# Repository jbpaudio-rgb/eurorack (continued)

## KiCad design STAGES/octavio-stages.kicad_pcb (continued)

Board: 2 copper layers, 242 parts (161 on the bottom side), 190 nets, no tracks yet.

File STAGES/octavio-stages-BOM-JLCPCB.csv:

Comment,Designator,Footprint,LCSC Part #,Notes
Raspberry Pi Pico,A1,RaspberryPi_Pico_Headers,,"Raspberry Pi Pico (RP2040) sur 2 barrettes femelles 1x20 2,54 mm, 8,5 mm (soudées à la main) - THT (wave soldering) - laisser JLC choisir (Basic de preference)"
10u 25V X5R/X7R 1206,"C1,C2,C3",C_1206_3216Metric,,X5R/X7R 1206 - SMT bottom - laisser JLC choisir (Basic de preference)
100p,"C16,C17",C_0603_1608Metric,,SMT bottom - laisser JLC choisir (Basic de preference)
10u 25V X5R/X7R 1206,C4,C_1206_3216Metric,,"X5R/X7R 1206 (3,3 V des potentiomètres) - SMT bottom - laisser JLC choisir (Basic de preference)"
100n,"C5,C6,C9,C10,C11,C12,C13,C14,C15,C18,C19,C20,C21,C22,C23,C24,C25",C_0603_1608Metric,,SMT bottom - laisser JLC choisir (Basic de preference)
10n,"C7,C8",C_0603_1608Metric,,SMT bottom - laisser JLC choisir (Basic de preference)
SS14,"D1,D2",D_SMA,,SS14 (40 V 1 A Schottky) - SMT bottom - laisser JLC choisir (Basic de preference)
LED,"D10,D11,D12,D13,D14,D15,D16,D17",LED_D3.0mm,,LED 3 mm ambre (SLIDE) - THT (wave soldering) - laisser JLC choisir (Basic de preference)
LED,"D20,D21,D22,D23,D24,D25,D26,D27",LED_D3.0mm,,LED 3 mm rouge (étape) - THT (wave soldering) - laisser JLC choisir (Basic de preference)
SS14,D3,D_SMA,,SS14 (Schottky : USB et rack peuvent être branchés ensemble) - SMT bottom - laisser JLC choisir (Basic de preference)
LED,"D30,D31,D32",LED_D3.0mm,,LED 3 mm ambre (mode) - THT (wave soldering) - laisser JLC choisir (Basic de preference)
BAT54S,"D4,D5",SOT-23,,BAT54S (protection ADC) - SMT bottom - laisser JLC choisir (Basic de preference)
Eurorack 2x5,J1,IDC-Header_2x05_P2.54mm_Vertical,,Shrouded header 2x5 2.54 mm - THT (wave soldering) - laisser JLC choisir (Basic de preference)
GATE,J10,Jack_3.5mm_Thonkiconn_PJ398SM,C9900080080,QingPu WQP-PJ301M-12 (Thonkiconn) - THT (wave soldering)
SEL 1,J11,Jack_3.5mm_Thonkiconn_PJ398SM,C9900080080,QingPu WQP-PJ301M-12 (Thonkiconn) - THT (wave soldering)
SEL 2,J12,Jack_3.5mm_Thonkiconn_PJ398SM,C9900080080,QingPu WQP-PJ301M-12 (Thonkiconn) - THT (wave soldering)
SEL 3,J13,Jack_3.5mm_Thonkiconn_PJ398SM,C9900080080,QingPu WQP-PJ301M-12 (Thonkiconn) - THT (wave soldering)
SEL 4,J14,Jack_3.5mm_Thonkiconn_PJ398SM,C9900080080,QingPu WQP-PJ301M-12 (Thonkiconn) - THT (wave soldering)
SEL 5,J15,Jack_3.5mm_Thonkiconn_PJ398SM,C9900080080,QingPu WQP-PJ301M-12 (Thonkiconn) - THT (wave soldering)
SEL 6,J16,Jack_3.5mm_Thonkiconn_PJ398SM,C9900080080,QingPu WQP-PJ301M-12 (Thonkiconn) - THT (wave soldering)
SEL 7,J17,Jack_3.5mm_Thonkiconn_PJ398SM,C9900080080,QingPu WQP-PJ301M-12 (Thonkiconn) - THT (wave soldering)
SEL 8,J18,Jack_3.5mm_Thonkiconn_PJ398SM,C9900080080,QingPu WQP-PJ301M-12 (Thonkiconn) - THT (wave soldering)
GATE 1,J19,Jack_3.5mm_Thonkiconn_PJ398SM,C9900080080,QingPu WQP-PJ301M-12 (Thonkiconn) - THT (wave soldering)
CLOCK,J2,Jack_3.5mm_Thonkiconn_PJ398SM,C9900080080,QingPu WQP-PJ301M-12 (Thonkiconn) - THT (wave soldering)
GATE 2,J20,Jack_3.5mm_Thonkiconn_PJ398SM,C9900080080,QingPu WQP-PJ301M-12 (Thonkiconn) - THT (wave soldering)
GATE 3,J21,Jack_3.5mm_Thonkiconn_PJ398SM,C9900080080,QingPu WQP-PJ301M-12 (Thonkiconn) - THT (wave soldering)
GATE 4,J22,Jack_3.5mm_Thonkiconn_PJ398SM,C9900080080,QingPu WQP-PJ301M-12 (Thonkiconn) - THT (wave soldering)
GATE 5,J23,Jack_3.5mm_Thonkiconn_PJ398SM,C9900080080,QingPu WQP-PJ301M-12 (Thonkiconn) - THT (wave soldering)
GATE 6,J24,Jack_3.5mm_Thonkiconn_PJ398SM,C9900080080,QingPu WQP-PJ301M-12 (Thonkiconn) - THT (wave soldering)
GATE 7,J25,Jack_3.5mm_Thonkiconn_PJ398SM,C9900080080,QingPu WQP-PJ301M-12 (Thonkiconn) - THT (wave soldering)
GATE 8,J26,Jack_3.5mm_Thonkiconn_PJ398SM,C9900080080,QingPu WQP-PJ301M-12 (Thonkiconn) - THT (wave soldering)
START,J3,Jack_3.5mm_Thonkiconn_PJ398SM,C9900080080,QingPu WQP-PJ301M-12 (Thonkiconn) - THT (wave soldering)
STROBE,J4,Jack_3.5mm_Thonkiconn_PJ398SM,C9900080080,QingPu WQP-PJ301M-12 (Thonkiconn) - THT (wave soldering)
TIME CV,J5,Jack_3.5mm_Thonkiconn_PJ398SM,C9900080080,QingPu WQP-PJ301M-12 (Thonkiconn) - THT (wave soldering)
ANALOG,J6,Jack_3.5mm_Thonkiconn_PJ398SM,C9900080080,QingPu WQP-PJ301M-12 (Thonkiconn) - THT (wave soldering)
END,J7,Jack_3.5mm_Thonkiconn_PJ398SM,C9900080080,QingPu WQP-PJ301M-12 (Thonkiconn) - THT (wave soldering)
CV A,J8,Jack_3.5mm_Thonkiconn_PJ398SM,C9900080080,QingPu WQP-PJ301M-12 (Thonkiconn) - THT (wave soldering)
CV B,J9,Jack_3.5mm_Thonkiconn_PJ398SM,C9900080080,QingPu WQP-PJ301M-12 (Thonkiconn) - THT (wave soldering)
BC847C,"Q1,Q2,Q3,Q4,Q5,Q6,Q7,Q8,Q9,Q10,Q11",SOT-23,,BC847C - SMT bottom - laisser JLC choisir (Basic de preference)
100k 1% 0805,"R1,R5,R9,R10,R12,R13,R15,R16,R18,R19,R21,R22,R24,R25,R27,R28,R30,R31,R33,R34,R36,R37,R39,R40",R_0603_1608Metric,,SMT bottom - laisser JLC choisir (Basic de preference)
38k3 1% 0805,"R100,R103",R_0603_1608Metric,,SMT bottom - laisser JLC choisir (Basic de preference)
10k 1% 0805,"R11,R14,R17,R20,R23,R26,R29,R32,R35,R38,R41,R42,R43,R44,R45,R46,R47,R48,R49,R69,R72,R75,R78,R81,R84,R87,R90,R93,R96,R99,R102",R_0603_1608Metric,,SMT bottom - laisser JLC choisir (Basic de preference)
15k 1% 0805,"R2,R6",R_0603_1608Metric,,SMT bottom - laisser JLC choisir (Basic de preference)
110k 1% 0805,"R3,R7",R_0603_1608Metric,,SMT bottom - laisser JLC choisir (Basic de preference)
1k 1% 0805,"R4,R8,R50,R51,R52,R53,R54,R55,R56,R57,R58,R59,R60,R61,R62,R63,R64,R65,R66,R67,R68,R71,R74,R77,R80,R83,R86,R89,R92,R95,R98,R101,R104",R_0603_1608Metric,,SMT bottom - laisser JLC choisir (Basic de preference)
20k 1% 0805,"R70,R73,R76,R79,R82,R85,R88,R91,R94,R97",R_0603_1608Metric,,SMT bottom - laisser JLC choisir (Basic de preference)
10k B,"RV1,RV2,RV3,RV4,RV5,RV6,RV7,RV8,RV9,RV10,RV11,RV12,RV13,RV14,RV15,RV16,RV17,RV18,RV19,RV20,RV21,RV22,RV23,RV24,RV25,RV26,RV27",Pot_Alpha_9mm_Vertical,,"POT-R09V-10K (9 mm vertical, B10k) - THT (wave soldering) - laisser JLC choisir (Basic de preference)"
SW,"SW1,SW2,SW3,SW4,SW5,SW6,SW7,SW8,SW9,SW10",Tactile_6mm_THT_Panel,,"Bouton 6x6 mm THT à tige longue (ex. TS-1187A-B-A-B / C&K PTS645, capuchon rond) - THT (wave soldering) - laisser JLC choisir (Basic de preference)"
AMS1117-5.0,U1,SOT-223-3_TabPin2,,AMS1117-5.0 (C6187) - SMT bottom - laisser JLC choisir (Basic de preference)
MCP4822-E/SN,U10,SOIC-8_3.9x4.9mm_P1.27mm,,MCP4822-E/SN - SMT bottom - laisser JLC choisir (Basic de preference)
TL074CDR,"U11,U12,U13,U14",SOIC-14_3.9x8.7mm_P1.27mm,C12594,TL074CDR - SMT bottom
74HC4067 CD74HC4067M96,"U2,U3",SOIC-24W_7.5x15.4mm_P1.27mm,,CD74HC4067M96 - SMT bottom - laisser JLC choisir (Basic de preference)
74HC165D,"U4,U5",SOIC-16_3.9x9.9mm_P1.27mm,,74HC165D - SMT bottom - laisser JLC choisir (Basic de preference)
74HC595D,"U6,U7,U8,U9",SOIC-16_3.9x9.9mm_P1.27mm,,74HC595D - SMT bottom - laisser JLC choisir (Basic de preference)

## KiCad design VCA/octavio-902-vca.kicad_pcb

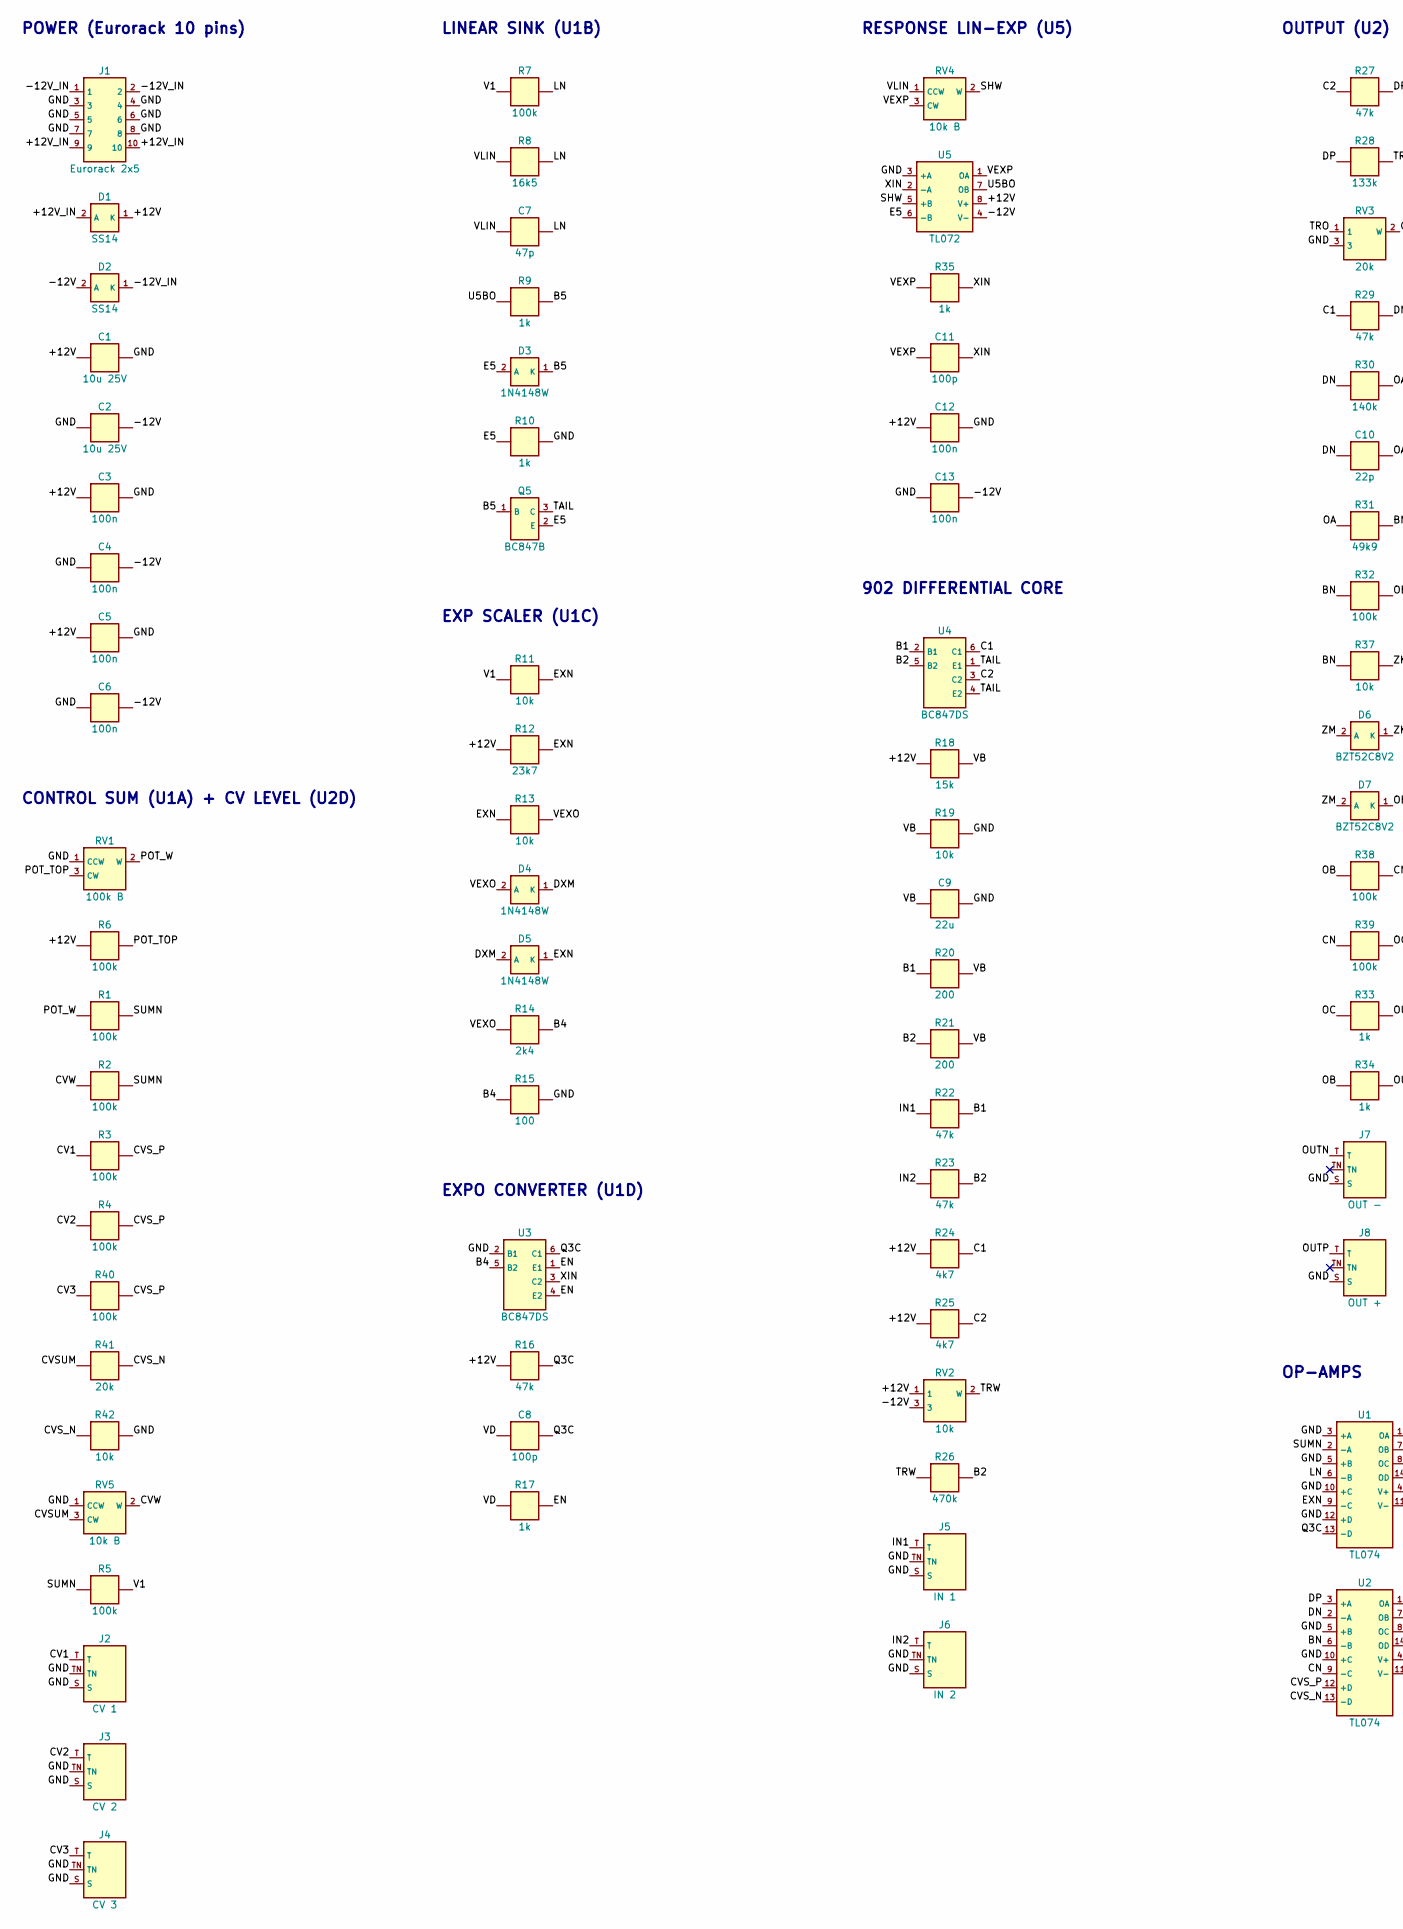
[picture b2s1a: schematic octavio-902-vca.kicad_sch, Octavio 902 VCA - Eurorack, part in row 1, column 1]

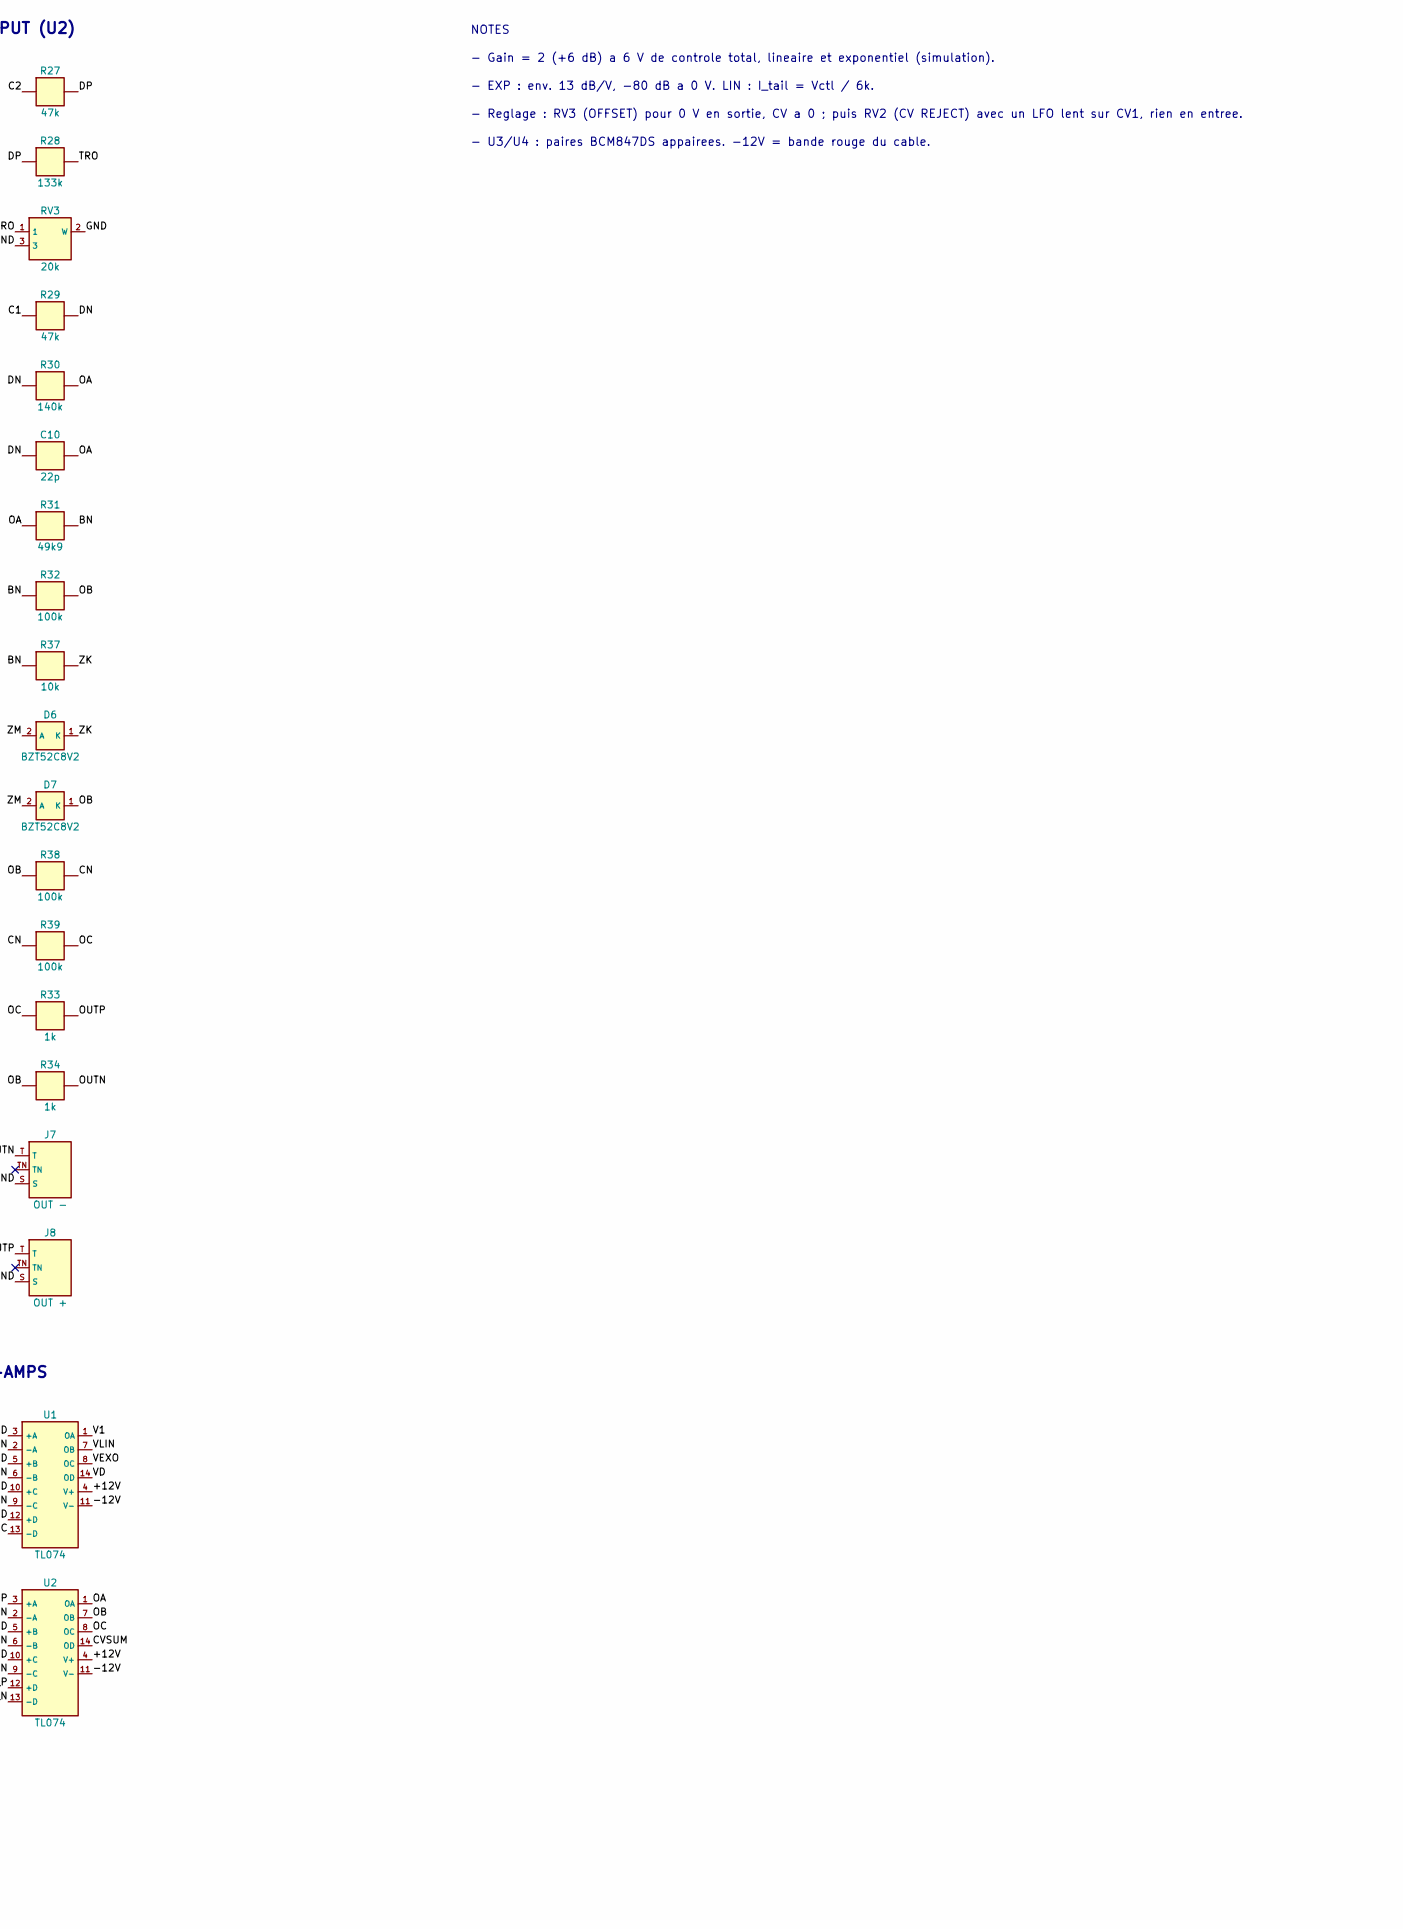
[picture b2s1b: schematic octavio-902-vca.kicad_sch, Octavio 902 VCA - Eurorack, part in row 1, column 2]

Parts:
C1, C2: 10u 25V; C_1206_3216Metric; MPN X5R/X7R 1206
C3, C4, C5, C6, C12, C13: 100n; C_0805_2012Metric
C7: 47p; C_0805_2012Metric
C8, C11: 100p; C_0805_2012Metric
C9: 22u; C_1206_3216Metric; MPN X5R 1206 16 V
C10: 22p; C_0805_2012Metric
D1, D2: SS14; D_SMA; MPN SS14 (40 V 1 A Schottky)
D3, D4, D5: 1N4148W; D_SOD-123; MPN 1N4148W
D6, D7: BZT52C8V2; D_SOD-123; MPN BZT52C8V2 (zener 8,2 V)
J1: Eurorack 2x5; IDC-Header_2x05_P2.54mm_Vertical; MPN Shrouded header 2x5 2.54 mm
J2: CV 1; Jack_3.5mm_Thonkiconn_PJ398SM; MPN QingPu WQP-PJ301M-12 (Thonkiconn)
J3: CV 2; Jack_3.5mm_Thonkiconn_PJ398SM; MPN QingPu WQP-PJ301M-12 (Thonkiconn)
J4: CV 3; Jack_3.5mm_Thonkiconn_PJ398SM; MPN QingPu WQP-PJ301M-12 (Thonkiconn)
J5: IN 1; Jack_3.5mm_Thonkiconn_PJ398SM; MPN QingPu WQP-PJ301M-12 (Thonkiconn)
J6: IN 2; Jack_3.5mm_Thonkiconn_PJ398SM; MPN QingPu WQP-PJ301M-12 (Thonkiconn)
J7: OUT -; Jack_3.5mm_Thonkiconn_PJ398SM; MPN QingPu WQP-PJ301M-12 (Thonkiconn)
J8: OUT +; Jack_3.5mm_Thonkiconn_PJ398SM; MPN QingPu WQP-PJ301M-12 (Thonkiconn)
Q5: BC847B; SOT-23; MPN BC847B
R1, R2, R3, R4, R5, R6, R7, R32, R38, R39, R40: 100k; R_0805_2012Metric
R8: 16k5; R_0805_2012Metric
R9, R10, R17, R33, R34, R35: 1k; R_0805_2012Metric
R11, R13, R19, R37, R42: 10k; R_0805_2012Metric
R12: 23k7; R_0805_2012Metric
R14: 2k4; R_0805_2012Metric
R15: 100; R_0805_2012Metric
R16, R22, R23, R27, R29: 47k; R_0805_2012Metric
R18: 15k; R_0805_2012Metric
R20, R21: 200; R_0805_2012Metric
R24, R25: 4k7; R_0805_2012Metric
R26: 470k; R_0805_2012Metric
R28: 133k; R_0805_2012Metric
R30: 140k; R_0805_2012Metric
R31: 49k9; R_0805_2012Metric
R41: 20k; R_0805_2012Metric
RV1: 100k B; Pot_Alpha_9mm_Vertical; MPN POT-R09V-100K (9 mm vertical, B100k)
RV2: 10k; Potentiometer_Bourns_3362P_Vertical; MPN Bourns 3362P-1-103LF
RV3: 20k; Potentiometer_Bourns_3362P_Vertical; MPN Bourns 3362P-1-203LF
RV4, RV5: 10k B; Pot_Alpha_9mm_Vertical; MPN POT-R09V-10K (9 mm vertical, B10k)
U1, U2: TL074; SOIC-14_3.9x8.7mm_P1.27mm; MPN TL074CDR
U3, U4: BC847DS; SOT-457; MPN BC847DS,115 (Nexperia, paire double)
U5: TL072; SOIC-8_3.9x4.9mm_P1.27mm; MPN TL072CDR

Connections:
+12V: C1.1, C3.1, C5.1, C12.1, D1.1 (K), R6.1, R12.1, R16.1, R18.1, R24.1, R25.1, RV2.1, U1.4 (V+), U2.4 (V+), U5.8 (V+)
+12V_IN: D1.2 (A), J1.9, J1.10
-12V: C2.2, C4.2, C6.2, C13.2, D2.2 (A), RV2.3, U1.11 (V-), U2.11 (V-), U5.4 (V-)
-12V_IN: D2.1 (K), J1.1, J1.2
B1: R20.1, R22.2, U4.2 (B1)
B2: R21.1, R23.2, R26.2, U4.5 (B2)
B4: R14.2, R15.1, U3.5 (B2)
B5: D3.1 (K), Q5.1 (B), R9.2
BN: R31.2, R32.1, R37.1, U2.6 (-B)
C1: R24.2, R29.1, U4.6 (C1)
C2: R25.2, R27.1, U4.3 (C2)
CN: R38.2, R39.1, U2.9 (-C)
CV1: J2.T, R3.1
CV2: J3.T, R4.1
CV3: J4.T, R40.1
CVSUM: R41.1, RV5.3 (CW), U2.14 (OD)
CVS_N: R41.2, R42.1, U2.13 (-D)
CVS_P: R3.2, R4.2, R40.2, U2.12 (+D)
CVW: R2.1, RV5.2 (W)
DN: C10.1, R29.2, R30.1, U2.2 (-A)
DP: R27.2, R28.1, U2.3 (+A)
DXM: D4.1 (K), D5.2 (A)
E5: D3.2 (A), Q5.2 (E), R10.1, U5.6 (-B)
EN: R17.2, U3.1 (E1), U3.4 (E2)
EXN: D5.1 (K), R11.2, R12.2, R13.1, U1.9 (-C)
GND: C1.2, C2.1, C3.2, C4.1, C5.2, C6.1, C9.2, C12.2, C13.1, J1.3, J1.4, J1.5, J1.6, J1.7, J1.8, J2.S, J2.TN, J3.S, J3.TN, J4.S, J4.TN, J5.S, J5.TN, J6.S, J6.TN, J7.S, J8.S, R10.2, R15.2, R19.2, R42.2, RV1.1 (CCW), RV3.2 (W), RV3.3, RV5.1 (CCW), U1.3 (+A), U1.5 (+B), U1.10 (+C), U1.12 (+D), U2.5 (+B), U2.10 (+C), U3.2 (B1), U5.3 (+A)
IN1: J5.T, R22.1
IN2: J6.T, R23.1
LN: C7.2, R7.2, R8.2, U1.6 (-B)
OA: C10.2, R30.2, R31.1, U2.1 (OA)
OB: D7.1 (K), R32.2, R34.1, R38.1, U2.7 (OB)
OC: R33.1, R39.2, U2.8 (OC)
OUTN: J7.T, R34.2
OUTP: J8.T, R33.2
POT_TOP: R6.2, RV1.3 (CW)
POT_W: R1.1, RV1.2 (W)
Q3C: C8.2, R16.2, U1.13 (-D), U3.6 (C1)
SHW: RV4.2 (W), U5.5 (+B)
SUMN: R1.2, R2.2, R5.1, U1.2 (-A)
TAIL: Q5.3 (C), U4.1 (E1), U4.4 (E2)
TRO: R28.2, RV3.1
TRW: R26.1, RV2.2 (W)
U5BO: R9.1, U5.7 (OB)
V1: R5.2, R7.1, R11.1, U1.1 (OA)
VB: C9.1, R18.2, R19.1, R20.2, R21.2
VD: C8.1, R17.1, U1.14 (OD)
VEXO: D4.2 (A), R13.2, R14.1, U1.8 (OC)
VEXP: C11.1, R35.1, RV4.3 (CW), U5.1 (OA)
VLIN: C7.1, R8.1, RV4.1 (CCW), U1.7 (OB)
XIN: C11.2, R35.2, U3.3 (C2), U5.2 (-A)
ZK: D6.1 (K), R37.2
ZM: D6.2 (A), D7.2 (A)

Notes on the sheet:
POWER (Eurorack 10 pins)
CONTROL SUM (U1A) + CV LEVEL (U2D)
LINEAR SINK (U1B)
EXP SCALER (U1C)
EXPO CONVERTER (U1D)
RESPONSE LIN-EXP (U5)
902 DIFFERENTIAL CORE
OUTPUT (U2)
OP-AMPS
NOTES
- Gain = 2 (+6 dB) a 6 V de controle total, lineaire et exponentiel (simulation).
- EXP : env. 13 dB/V, -80 dB a 0 V. LIN : I_tail = Vctl / 6k.
- Reglage : RV3 (OFFSET) pour 0 V en sortie, CV a 0 ; puis RV2 (CV REJECT) avec un LFO lent sur CV1, rien en entree.
- U3/U4 : paires BCM847DS appairees. -12V = bande rouge du cable.

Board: 2 copper layers, 80 parts (70 on the bottom side), 52 nets, no tracks yet.

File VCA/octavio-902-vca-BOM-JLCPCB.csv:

Comment,Designator,Footprint,LCSC Part #,Notes
10u 25V X5R/X7R 1206,"C1,C2",C_1206_3216Metric,,X5R/X7R 1206 - SMT bottom - laisser JLC choisir (Basic de preference)
22p,C10,C_0805_2012Metric,,SMT bottom - laisser JLC choisir (Basic de preference)
100n,"C3,C4,C5,C6,C12,C13",C_0805_2012Metric,,SMT bottom - laisser JLC choisir (Basic de preference)
47p,C7,C_0805_2012Metric,,SMT bottom - laisser JLC choisir (Basic de preference)
100p,"C8,C11",C_0805_2012Metric,,SMT bottom - laisser JLC choisir (Basic de preference)
22u X5R 1206 16 V,C9,C_1206_3216Metric,,X5R 1206 16 V - SMT bottom - laisser JLC choisir (Basic de preference)
SS14,"D1,D2",D_SMA,,SS14 (40 V 1 A Schottky) - SMT bottom - laisser JLC choisir (Basic de preference)
1N4148W,"D3,D4,D5",D_SOD-123,,1N4148W - SMT bottom - laisser JLC choisir (Basic de preference)
BZT52C8V2,"D6,D7",D_SOD-123,,"BZT52C8V2 (zener 8,2 V) - SMT bottom - laisser JLC choisir (Basic de preference)"
Eurorack 2x5,J1,IDC-Header_2x05_P2.54mm_Vertical,,Shrouded header 2x5 2.54 mm - THT (wave soldering) - laisser JLC choisir (Basic de preference)
CV 1,J2,Jack_3.5mm_Thonkiconn_PJ398SM,C9900080080,QingPu WQP-PJ301M-12 (Thonkiconn) - THT (wave soldering)
CV 2,J3,Jack_3.5mm_Thonkiconn_PJ398SM,C9900080080,QingPu WQP-PJ301M-12 (Thonkiconn) - THT (wave soldering)
CV 3,J4,Jack_3.5mm_Thonkiconn_PJ398SM,C9900080080,QingPu WQP-PJ301M-12 (Thonkiconn) - THT (wave soldering)
IN 1,J5,Jack_3.5mm_Thonkiconn_PJ398SM,C9900080080,QingPu WQP-PJ301M-12 (Thonkiconn) - THT (wave soldering)
IN 2,J6,Jack_3.5mm_Thonkiconn_PJ398SM,C9900080080,QingPu WQP-PJ301M-12 (Thonkiconn) - THT (wave soldering)
OUT -,J7,Jack_3.5mm_Thonkiconn_PJ398SM,C9900080080,QingPu WQP-PJ301M-12 (Thonkiconn) - THT (wave soldering)
OUT +,J8,Jack_3.5mm_Thonkiconn_PJ398SM,C9900080080,QingPu WQP-PJ301M-12 (Thonkiconn) - THT (wave soldering)
BC847B,Q5,SOT-23,,BC847B - SMT bottom - laisser JLC choisir (Basic de preference)
23k7 1% 0805,R12,R_0805_2012Metric,,SMT bottom - laisser JLC choisir (Basic de preference)
2k4 1% 0805,R14,R_0805_2012Metric,,SMT bottom - laisser JLC choisir (Basic de preference)
100 1% 0805,R15,R_0805_2012Metric,,SMT bottom - laisser JLC choisir (Basic de preference)
47k 1% 0805,"R16,R22,R23,R27,R29",R_0805_2012Metric,,SMT bottom - laisser JLC choisir (Basic de preference)
15k 1% 0805,R18,R_0805_2012Metric,,SMT bottom - laisser JLC choisir (Basic de preference)
200 1% 0805,"R20,R21",R_0805_2012Metric,,SMT bottom - laisser JLC choisir (Basic de preference)
4k7 1% 0805,"R24,R25",R_0805_2012Metric,,SMT bottom - laisser JLC choisir (Basic de preference)
470k 1% 0805,R26,R_0805_2012Metric,,SMT bottom - laisser JLC choisir (Basic de preference)
133k 1% 0805,R28,R_0805_2012Metric,,SMT bottom - laisser JLC choisir (Basic de preference)
140k 1% 0805,R30,R_0805_2012Metric,,SMT bottom - laisser JLC choisir (Basic de preference)
49k9 1% 0805,R31,R_0805_2012Metric,,SMT bottom - laisser JLC choisir (Basic de preference)
20k 1% 0805,R41,R_0805_2012Metric,,SMT bottom - laisser JLC choisir (Basic de preference)
10k 1% 0805,"R42,R11,R13,R19,R37",R_0805_2012Metric,,SMT bottom - laisser JLC choisir (Basic de preference)
100k 1% 0805,"R6,R1,R2,R3,R4,R40,R5,R7,R32,R38,R39",R_0805_2012Metric,,SMT bottom - laisser JLC choisir (Basic de preference)
16k5 1% 0805,R8,R_0805_2012Metric,,SMT bottom - laisser JLC choisir (Basic de preference)
1k 1% 0805,"R9,R10,R17,R35,R33,R34",R_0805_2012Metric,,SMT bottom - laisser JLC choisir (Basic de preference)
100k B,RV1,Pot_Alpha_9mm_Vertical,C9900018037,"POT-R09V-100K (9 mm vertical, B100k) - THT (wave soldering)"
10k,RV2,Potentiometer_Bourns_3362P_Vertical,,Bourns 3362P-1-103LF - THT (wave soldering) - laisser JLC choisir (Basic de preference)
20k,RV3,Potentiometer_Bourns_3362P_Vertical,,Bourns 3362P-1-203LF - THT (wave soldering) - laisser JLC choisir (Basic de preference)
10k B,"RV5,RV4",Pot_Alpha_9mm_Vertical,,"POT-R09V-10K (9 mm vertical, B10k) - THT (wave soldering) - laisser JLC choisir (Basic de preference)"
TL074CDR,"U1,U2",SOIC-14_3.9x8.7mm_P1.27mm,C12594,TL074CDR - SMT bottom
"BC847DS,115","U3,U4",SOT-457,C549489,"BC847DS,115 (Nexperia, paire double) - SMT bottom"
TL072CDR,U5,SOIC-8_3.9x4.9mm_P1.27mm,,TL072CDR - SMT bottom - laisser JLC choisir (Basic de preference)

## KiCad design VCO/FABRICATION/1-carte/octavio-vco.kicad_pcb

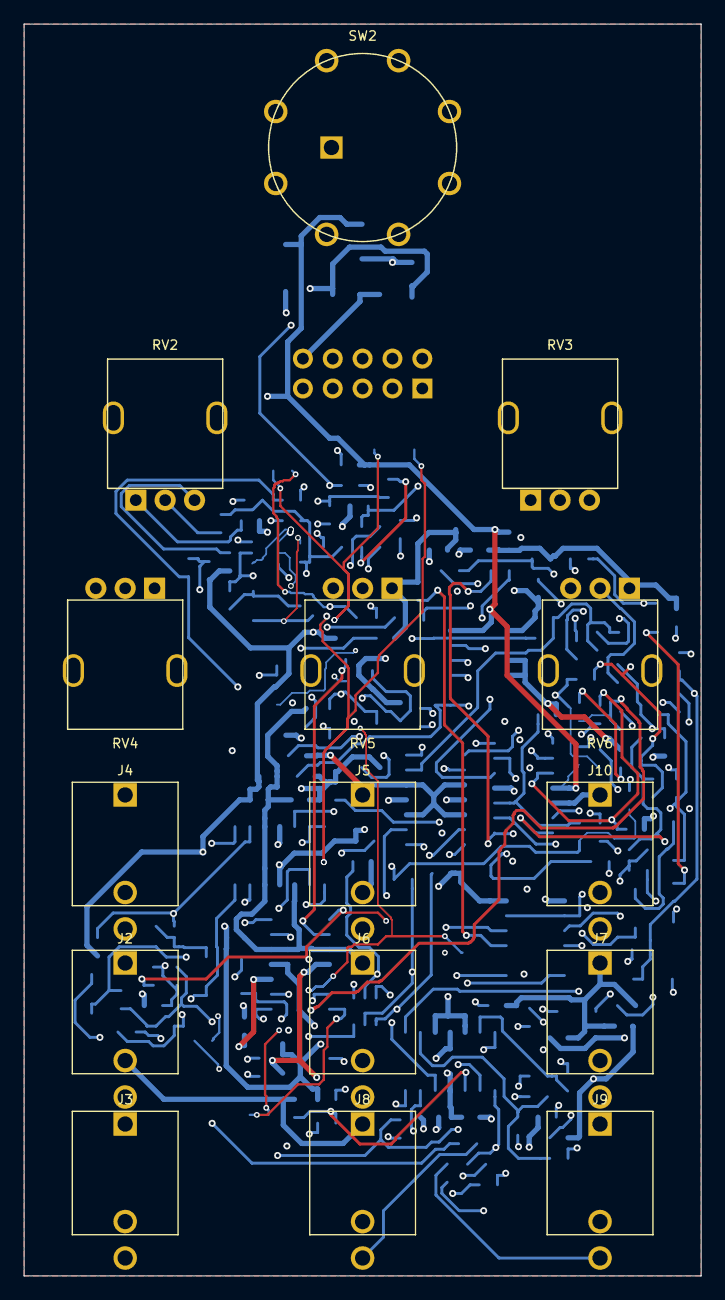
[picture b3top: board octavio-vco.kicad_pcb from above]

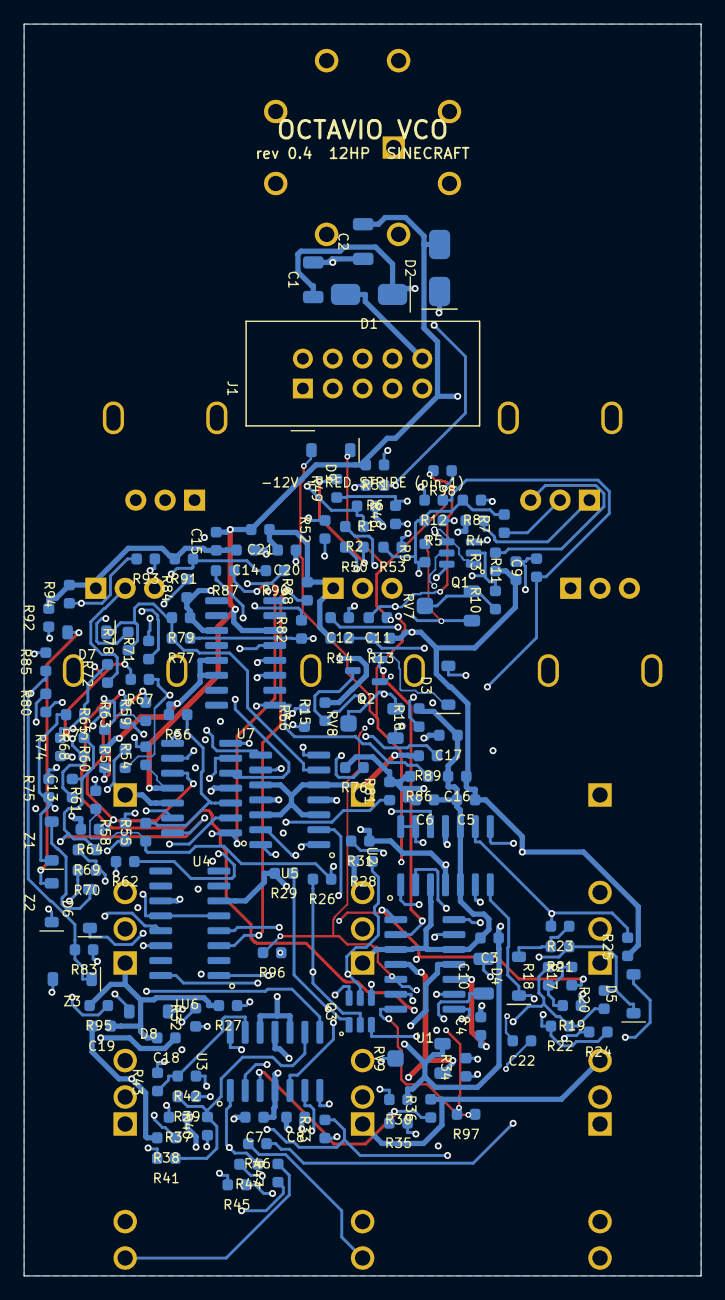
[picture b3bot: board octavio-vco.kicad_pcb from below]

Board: 4 copper layers, 57.6 x 106.5 mm, 161 parts (146 on the bottom side), 100 nets.

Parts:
C1, C2: 10u 25V; C_1206_3216Metric
C3, C4, C5, C6, C7, C8, C14, C15, C16, C17, C18, C19, C20, C21: 100n; C_0603_1608Metric
C9: 100p; C_0603_1608Metric
C10: 10n C0G; C_1206_3216Metric
C11: 220p; C_0603_1608Metric
C12: 1n; C_0603_1608Metric
C13: 47p; C_0603_1608Metric
C22: 330p; C_0603_1608Metric
D1, D2: SS14; D_SMA
D3, D4, D5, D6, D7, D8, D9: 1N4148W; D_SOD-123
J1: Eurorack 2x5; IDC-Header_2x05_P2.54mm_Vertical
J2: 1V/OCT; Jack_3.5mm_Thonkiconn_PJ398SM
J3: SYNC; Jack_3.5mm_Thonkiconn_PJ398SM
J4: FM; Jack_3.5mm_Thonkiconn_PJ398SM
J5: PWM; Jack_3.5mm_Thonkiconn_PJ398SM
J6: SINE; Jack_3.5mm_Thonkiconn_PJ398SM
J7: TRIANGLE; Jack_3.5mm_Thonkiconn_PJ398SM
J8: SAW; Jack_3.5mm_Thonkiconn_PJ398SM
J9: PULSE; Jack_3.5mm_Thonkiconn_PJ398SM
J10: BLEND OUT; Jack_3.5mm_Thonkiconn_PJ398SM
Q1, Q3: BC847DS; SOT-457
Q2: MMBFJ112; SOT-23
R1, R14, R16, R17, R20, R21, R23, R39, R41, R43, R55, R56, R57, R58, R59, R60, R61, R62, R63, R64, R65, R66, R69, R70, R72, R77, R82, R96: 10k; R_0603_1608Metric
R2, R6, R48, R49: 1k 0.1%; R_0603_1608Metric
R3, R4: 7k15; R_0603_1608Metric
R5, R53: 100k 0.1%; R_0603_1608Metric
R7, R32, R97: 1M; R_0603_1608Metric
R8, R52: 100k; R_0603_1608Metric
R9: 1k TC; R_0603_1608Metric
R10, R27, R28: 680; R_0603_1608Metric
R11: 910k; R_0603_1608Metric
R12, R44, R45, R46, R47, R71: 1k; R_0603_1608Metric
R13: 14k; R_0603_1608Metric
R15, R42, R67, R68: 22k; R_0603_1608Metric
R18, R22: 20k; R_0603_1608Metric
R19: 48k7; R_0603_1608Metric
R24: 40k2; R_0603_1608Metric
R25: 95k3; R_0603_1608Metric
R26, R30, R31, R87, R90, R93: 47k; R_0603_1608Metric
R29: 113k; R_0603_1608Metric
R33, R35: 470k; R_0603_1608Metric
R34, R36: 560k; R_0603_1608Metric
R37: 562; R_0603_1608Metric
R38: 16k2; R_0603_1608Metric
R40: 22k1; R_0603_1608Metric
R50: 4k99 0.1%; R_0603_1608Metric
R51: 4k99; R_0603_1608Metric
R54: 2k; R_0603_1608Metric
R73, R78, R83: 25k5; R_0603_1608Metric
R74: 93k1; R_0603_1608Metric
R75, R80, R85: 7k5; R_0603_1608Metric
R76, R81, R86: 1k2; R_0603_1608Metric
R79: 26k1; R_0603_1608Metric
R84: 15k4; R_0603_1608Metric
R88, R89, R91, R92, R94, R95: 100; R_0603_1608Metric
R98: 4k7; R_0603_1608Metric
RV2, RV3, RV4, RV5, RV6: 10k B; Pot_Alpha_9mm_Vertical
RV7: 500; Trim_SMD_Bourns_3314J
RV8, RV9: 1k; Trim_SMD_Bourns_3314J
SW2: RANGE; Rotary_SR16_1P8T
U1, U2, U3, U4, U5: TL074; SOIC-14_3.9x8.7mm_P1.27mm
U6, U7: LM13700; SOIC-16_3.9x9.9mm_P1.27mm
Z1, Z2, Z3: BZT52C5V1; D_SOD-123

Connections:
+12V: C1.1, C3.1, C5.1, C7.1, C14.1, C16.1, C18.1, C20.1, D1.1, R1.1, R3.1, R11.1, R13.1, R25.1, R30.1, R31.1, R74.1, R79.1, R84.1, RV9.3, U1.4, U2.4, U3.4, U4.4, U5.4, U6.11, U7.11
+12V_IN: D1.2, J1.9, J1.10
-12V: C2.2, C4.2, C6.2, C8.2, C15.2, C17.2, C19.2, C21.2, D2.2, R4.2, R15.2, R19.1, R29.2, R38.2, R51.2, R54.1, R76.2, R81.2, R86.2, RV9.1, U1.11, U2.11, U3.11, U4.11, U5.11, U6.6, U7.6
-12V_IN: D2.1, J1.1, J1.2
BIN: R69.2, R70.1, U5.13
BLJ: J10.T, R71.2
BOUT: R70.2, R71.1, U5.14
BSUM: C13.2, R68.2, R69.1, U4.14
CMPP: C22.2, D3.1, R96.2, R97.2, U1.12
D1N: R57.2, R58.1, U4.2
D1O: R58.2, R87.1, U4.1
D1P: R55.2, R56.1, U4.3
D2N: R61.2, R62.1, U4.6
D2O: R62.2, R90.1, U4.7
D2P: R59.2, R60.1, U4.5
D3N: R65.2, R66.1, U4.9
D3O: R66.2, R93.1, U4.8
D3P: R63.2, R64.1, U4.10
EN: Q1.1, Q1.4, R12.2
FB1: R9.2, RV7.1
FB2: R10.1, RV7.2, RV7.3
FMJ: J4.T, RV4.3
FM_W: R8.1, RV4.2
GATE: C11.2, Q2.3, R15.1, R98.2
GND: C1.2, C2.1, C3.2, C4.1, C5.2, C6.1, C7.2, C8.1, C14.2, C15.1, C16.2, C17.1, C18.2, C19.1, C20.2, C21.1, J1.3, J1.4, J1.5, J1.6, J1.7, J1.8, J2.S, J2.TN, J3.S, J3.TN, J4.S, J4.TN, J5.S, J5.TN, J6.S, J7.S, J8.S, J9.S, J10.S, Q1.5, R14.2, R16.2, R27.2, R28.2, R36.2, R37.1, R56.2, R60.2, R64.2, R88.2, R89.2, R91.2, R92.2, R94.2, R95.2, RV4.1, RV5.1, RV6.1, U1.3, U1.5, U1.10, U2.3, U2.5, U2.10, U3.10, U3.12, U4.12, U5.3, U5.5, U5.10, U5.12, U7.13, U7.14
GX: C11.1, D9.1, R98.1
HFC: C10.2, Q2.1, RV8.1
HWA: D4.1, D5.2, U2.7
HWN: D5.1, R20.2, R21.1, U2.6
HWO: D4.2, R21.2, R23.1
IABC1: R75.2, R76.1, U6.1
IABC2: R80.2, R81.1, U6.16
IABC3: R85.2, R86.1, U7.1
INTN: C10.1, Q1.3, Q2.2, U1.9
K1N: D6.1, R72.2, R73.1, R74.2, U5.2
K1O: R73.2, R75.1, U5.1, Z1.1
K2N: D7.1, R77.2, R78.1, R79.2, U5.6
K2O: R78.2, R80.1, U5.7, Z2.1
K3N: D8.1, R82.2, R83.1, R84.2, U5.9
K3O: R83.2, R85.1, U5.8, Z3.1
KBT: R54.2, RV6.3
KB_W: R72.1, R77.1, R82.1, RV6.2
KNB: R4.1, RV2.1
KNT: R3.2, RV2.3
KN_W: R7.1, RV2.2
KWA: R37.2, RV3.1
KWB: R38.1, RV3.3
KW_W: R39.1, RV3.2
N0: R6.2, R48.1, R52.2, SW2.4
N1: R2.2, R6.1, SW2.5
N2: R1.2, R2.1, SW2.6
NM1: R48.2, R49.1, SW2.3
NM2: R49.2, R50.1, SW2.2
NM7: R50.2, R51.1, SW2.1
O1N: R89.1, U6.4
O1P: R87.2, R88.1, U6.3
O2N: R92.1, U6.13
O2P: R90.2, R91.1, U6.14
O3N: R95.1, U7.4
O3P: R93.2, R94.1, U7.3
PCMP: R42.1, U3.7
PON: R42.2, R43.1, U3.13
PULJ: J9.T, R47.2
PULO: R43.2, R47.1, R63.1, U3.14
PWMJ: J5.T, RV5.3
PWM_W: R40.1, RV5.2
QRC: C9.2, Q1.6, R11.2, U1.6
RAMP: R17.1, R96.1, RV8.2, RV8.3, U1.8, U3.5
REF5: R13.2, R14.1, U1.13
RNGB: R53.1, U2.13, U2.14
RNGC: R52.1, SW2.C, U2.12
RSTQ: C22.1, D9.2, R97.1, U1.14
SAWJ: J8.T, R46.2
SAWN: R17.2, R18.1, R19.2, U2.2
SAWO: R18.2, R20.1, R22.1, R46.1, R59.1, R65.1, U2.1
SB1: Q3.2, R26.2, R27.1
SB2: Q3.5, R28.1, R32.2
SC1: Q3.6, R30.2, R33.1
SC2: Q3.3, R31.2, R35.1
SE: Q3.1, Q3.4, R29.1
SINJ: J6.T, R44.2
SINO: R34.2, R44.1, R57.1, R67.1, U3.1
SINT: R32.1, RV9.2
SIN_N: R33.2, R34.1, U3.2
SIN_P: R35.2, R36.1, U3.3
SN: R5.2, R7.2, R8.2, R9.1, R53.2, U1.2
SUMB: C13.1, R67.2, R68.1, U4.13, U6.5, U6.12, U7.5
SYD: C12.2, D3.2, R16.1
SYNCJ: C12.1, J3.T
TRIJ: J7.T, R45.2
TRIO: R24.2, R26.1, R45.1, R55.1, R61.1, U2.8
TRN: R22.2, R23.2, R24.1, R25.2, U2.9
VD: C9.1, R12.1, U1.7
VOCTJ: J2.T, R5.1
VREFB: Q1.2, R10.2, U1.1
WID: R41.2, U3.6, U3.8
WN: R39.2, R40.2, R41.1, U3.9
ZM1: D6.2, Z1.2
ZM2: D7.2, Z2.2
ZM3: D8.2, Z3.2

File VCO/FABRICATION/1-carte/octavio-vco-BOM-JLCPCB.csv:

Comment,Designator,Footprint,LCSC Part #,Notes
10u 25V X5R/X7R 1206,"C1,C2",C_1206_3216Metric,,X5R/X7R 1206 - SMT bottom - laisser JLC choisir (Basic de preference)
10n C0G 10 nF C0G/NP0 1206,C10,C_1206_3216Metric,,10 nF C0G/NP0 1206 (condensateur de timing) - SMT bottom - laisser JLC choisir (Basic de preference)
220p,C11,C_0603_1608Metric,,SMT bottom - laisser JLC choisir (Basic de preference)
1n,C12,C_0603_1608Metric,,SMT bottom - laisser JLC choisir (Basic de preference)
47p,C13,C_0603_1608Metric,,SMT bottom - laisser JLC choisir (Basic de preference)
100n,"C3,C4,C5,C6,C7,C8,C14,C15,C16,C17,C18,C19,C20,C21",C_0603_1608Metric,,SMT bottom - laisser JLC choisir (Basic de preference)
100p,C9,C_0603_1608Metric,,SMT bottom - laisser JLC choisir (Basic de preference)
SS14,"D1,D2",D_SMA,,SS14 (40 V 1 A Schottky) - SMT bottom - laisser JLC choisir (Basic de preference)
1N4148W,"D3,D4,D5,D6,D7,D8,D9",D_SOD-123,,1N4148W - SMT bottom - laisser JLC choisir (Basic de preference)
"BC847DS,115","Q1,Q3",SOT-457,C549489,"BC847DS,115 (Nexperia, paire double) - SMT bottom"
MMBFJ112,Q2,SOT-23,,"MMBFJ112 (JFET N, D-S-G) - SMT bottom - laisser JLC choisir (Basic de preference)"
10k 1% 0603,"R1,R14,R16,R17,R20,R21,R23,R39,R41,R43,R55,R56,R57,R58,R59,R60,R61,R62,R63,R64,R65,R66,R69,R70,R72,R77,R82,R96",R_0603_1608Metric,,SMT bottom - laisser JLC choisir (Basic de preference)
680 1% 0603,"R10,R27,R28",R_0603_1608Metric,,SMT bottom - laisser JLC choisir (Basic de preference)
910k 1% 0603,R11,R_0603_1608Metric,,SMT bottom - laisser JLC choisir (Basic de preference)
1k 1% 0603,"R12,R44,R45,R46,R47,R71",R_0603_1608Metric,,SMT bottom - laisser JLC choisir (Basic de preference)
14k 1% 0603,R13,R_0603_1608Metric,,SMT bottom - laisser JLC choisir (Basic de preference)
22k 1% 0603,"R15,R42,R67,R68",R_0603_1608Metric,,SMT bottom - laisser JLC choisir (Basic de preference)
20k 1% 0603,"R18,R22",R_0603_1608Metric,,SMT bottom - laisser JLC choisir (Basic de preference)
48k7 1% 0603,R19,R_0603_1608Metric,,SMT bottom - laisser JLC choisir (Basic de preference)
1k 0.1% 0603,"R2,R6,R48,R49",R_0603_1608Metric,,"1k 0,1 % 25 ppm - SMT bottom - laisser JLC choisir (Basic de preference)"
40k2 1% 0603,R24,R_0603_1608Metric,,SMT bottom - laisser JLC choisir (Basic de preference)
95k3 1% 0603,R25,R_0603_1608Metric,,SMT bottom - laisser JLC choisir (Basic de preference)
47k 1% 0603,"R26,R30,R31,R87,R90,R93",R_0603_1608Metric,,SMT bottom - laisser JLC choisir (Basic de preference)
113k 1% 0603,R29,R_0603_1608Metric,,SMT bottom - laisser JLC choisir (Basic de preference)
7k15 1% 0603,"R3,R4",R_0603_1608Metric,,SMT bottom - laisser JLC choisir (Basic de preference)
562 1% 0603,R37,R_0603_1608Metric,,SMT bottom - laisser JLC choisir (Basic de preference)
16k2 1% 0603,R38,R_0603_1608Metric,,SMT bottom - laisser JLC choisir (Basic de preference)
22k1 1% 0603,R40,R_0603_1608Metric,,SMT bottom - laisser JLC choisir (Basic de preference)
100k 0.1% 0603,R5,R_0603_1608Metric,,"100k 0,1 % 25 ppm (précision 1 V/oct) - SMT bottom - laisser JLC choisir (Basic de preference)"
4k99 0.1% 0603,R50,R_0603_1608Metric,,"4k99 0,1 % 25 ppm - SMT bottom - laisser JLC choisir (Basic de preference)"
4k99 1% 0603,R51,R_0603_1608Metric,,SMT bottom - laisser JLC choisir (Basic de preference)
100k 1% 0603,"R8,R52",R_0603_1608Metric,,SMT bottom - laisser JLC choisir (Basic de preference)
100k 0.1% 0603,R53,R_0603_1608Metric,,"100k 0,1 % 25 ppm - SMT bottom - laisser JLC choisir (Basic de preference)"
2k 1% 0603,R54,R_0603_1608Metric,,SMT bottom - laisser JLC choisir (Basic de preference)
1M 1% 0603,"R7,R32,R97",R_0603_1608Metric,,SMT bottom - laisser JLC choisir (Basic de preference)
25k5 1% 0603,"R73,R78,R83",R_0603_1608Metric,,SMT bottom - laisser JLC choisir (Basic de preference)
93k1 1% 0603,R74,R_0603_1608Metric,,SMT bottom - laisser JLC choisir (Basic de preference)
7k5 1% 0603,"R75,R80,R85",R_0603_1608Metric,,SMT bottom - laisser JLC choisir (Basic de preference)
1k2 1% 0603,"R76,R81,R86",R_0603_1608Metric,,SMT bottom - laisser JLC choisir (Basic de preference)
26k1 1% 0603,R79,R_0603_1608Metric,,SMT bottom - laisser JLC choisir (Basic de preference)
15k4 1% 0603,R84,R_0603_1608Metric,,SMT bottom - laisser JLC choisir (Basic de preference)
100 1% 0603,"R88,R89,R91,R92,R94,R95",R_0603_1608Metric,,SMT bottom - laisser JLC choisir (Basic de preference)
1k 1% 0603,R9,R_0603_1608Metric,,"1k +3300 ppm/K (thermistance de compensation, collée à Q1) - SMT bottom - laisser JLC choisir (Basic de preference)"
500 Bourns 3314J-1-501E,RV7,Trim_SMD_Bourns_3314J,,"Bourns 3314J-1-501E (trimmer CMS, réglage V/OCT) - SMT bottom - laisser JLC choisir (Basic de preference)"
1k Bourns 3314J-1-102E,RV8,Trim_SMD_Bourns_3314J,,"Bourns 3314J-1-102E (trimmer CMS, réglage HF) - SMT bottom - laisser JLC choisir (Basic de preference)"
1k Bourns 3314J-1-102E,RV9,Trim_SMD_Bourns_3314J,,"Bourns 3314J-1-102E (trimmer CMS, symétrie du sinus) - SMT bottom - laisser JLC choisir (Basic de preference)"
TL074CDR,"U1,U2,U3,U4,U5",SOIC-14_3.9x8.7mm_P1.27mm,C12594,TL074CDR - SMT bottom
LM13700MX/NOPB,"U6,U7",SOIC-16_3.9x9.9mm_P1.27mm,,LM13700MX/NOPB - SMT bottom - laisser JLC choisir (Basic de preference)
BZT52C5V1,"Z1,Z2,Z3",D_SOD-123,,"BZT52C5V1 (zener 5,1 V) - SMT bottom - laisser JLC choisir (Basic de preference)"
470k 1% 0603,"R33,R35",R_0603_1608Metric,,SMT bottom - laisser JLC choisir (Basic de preference)
560k 1% 0603,"R34,R36",R_0603_1608Metric,,SMT bottom - laisser JLC choisir (Basic de preference)
330p C0G 0603,C22,C_0603_1608Metric,,SMT bottom - laisser JLC choisir (Basic de preference)
4k7 1% 0603,R98,R_0603_1608Metric,,SMT bottom - laisser JLC choisir (Basic de preference)
